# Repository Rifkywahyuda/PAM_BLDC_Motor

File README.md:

# PAM_BLDC_Motor
About design of PCB of Pulse Amplitude Modulation 
1. File "inverter#3" is a PCB controller that drive inverter 3 phase and buck converter to run motor BLDC
2. File "Buck#3" is a PCB mosfet area

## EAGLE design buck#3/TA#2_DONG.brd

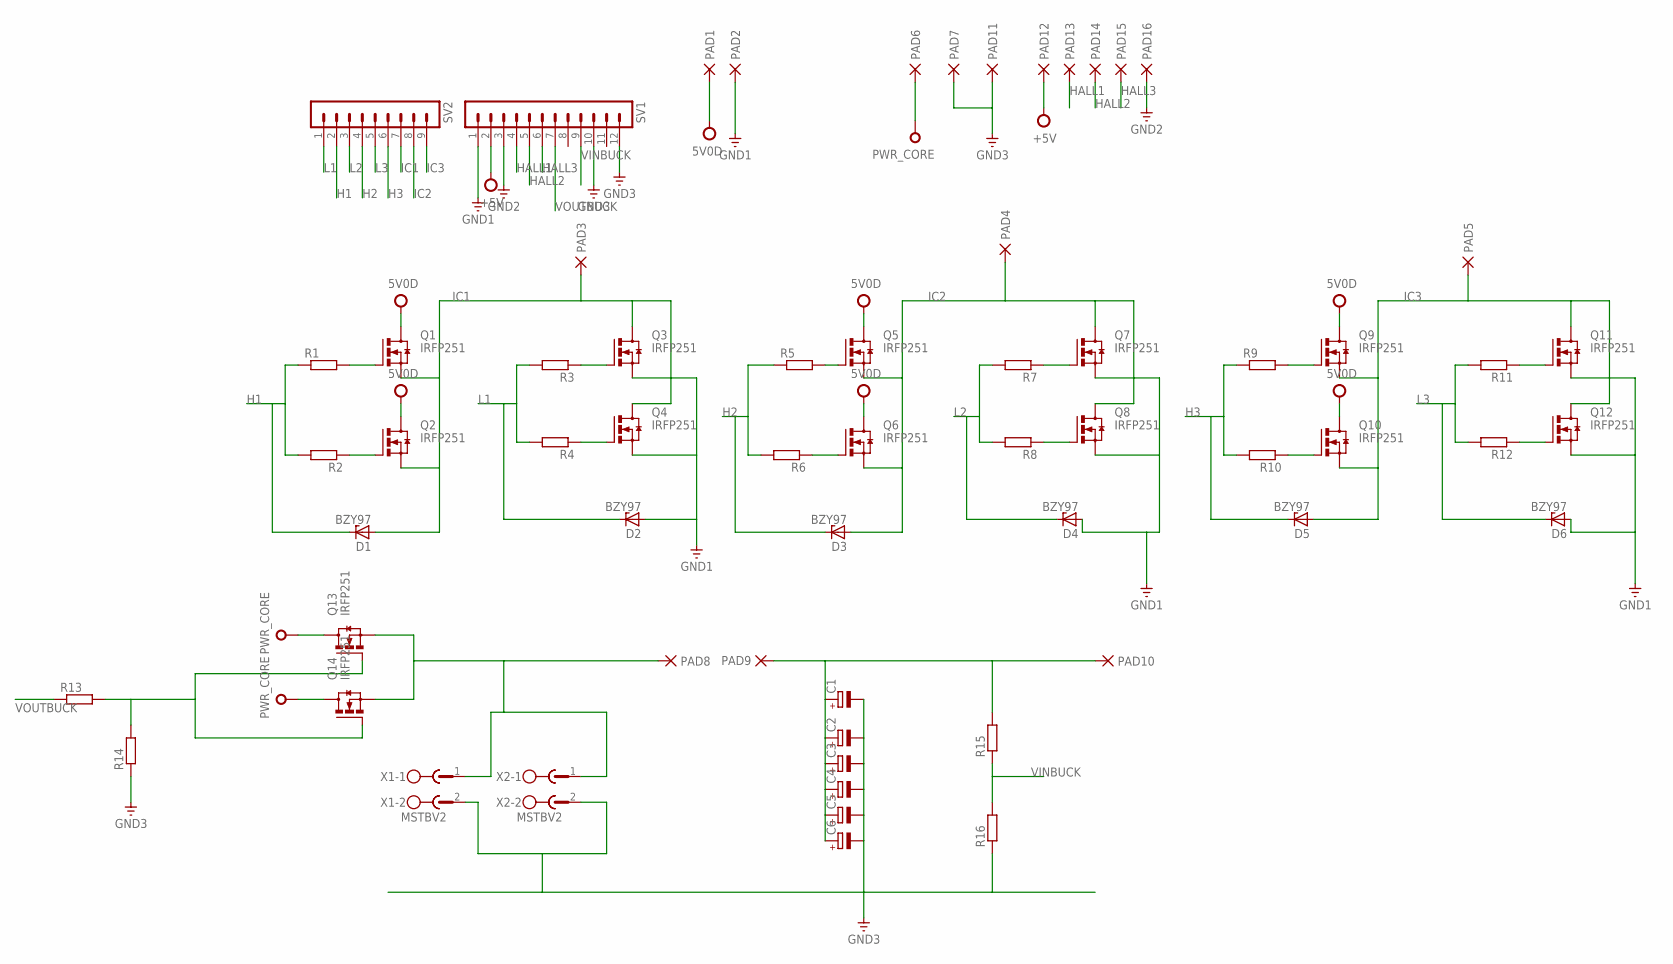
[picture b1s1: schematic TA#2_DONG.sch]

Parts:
C1, C2, C3, C4, C5, C6: CPOL-EUTT5D9; TT5D9
D1, D2, D3, D4, D5, D6: BZY97; F126Z12
PAD1, PAD2, PAD3, PAD4, PAD5, PAD6, PAD7, PAD8, PAD9, PAD10, PAD11, PAD12, PAD13, PAD14, PAD15, PAD16: PAD-0820; 0820
Q1, Q2, Q3, Q4, Q5, Q6, Q7, Q8, Q9, Q10, Q11, Q12, Q13, Q14: IRFP251; TO-247AD-V
R1, R2, R3, R4, R5, R6, R7, R8, R9, R10, R11, R12, R13, R14, R15, R16: R-EU_0207/15; 0207/15
SV1: MA12-1
SV2: MA09-1
X1, X2: MSTBV2

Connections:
5V0D: PAD1.P$1, Q1.D, Q2.D, Q5.D, Q6.D, Q9.D, Q10.D
+5V: PAD12.P$1, SV1.2
GND1: D2.A, D4.A, D6.A, PAD2.P$1, Q3.S, Q4.S, Q7.S, Q8.S, Q11.S, Q12.S, SV1.1
GND2: PAD16.P$1, SV1.3
GND3: C1.-, C2.-, C3.-, C4.-, C5.-, C6.-, PAD7.P$1, PAD11.P$1, R14.1, R16.1, SV1.10, SV1.12, X1.2, X2.2
H1: D1.C, R1.1, R2.2, SV2.2
H2: D3.C, R5.1, R6.2, SV2.4
H3: D5.C, R9.1, R10.2, SV2.6
HALL1: PAD13.P$1, SV1.4
HALL2: PAD14.P$1, SV1.5
HALL3: PAD15.P$1, SV1.6
IC1: D1.A, PAD3.P$1, Q1.S, Q2.S, Q3.D, Q4.D, SV2.7
IC2: D3.A, PAD4.P$1, Q5.S, Q6.S, Q7.D, Q8.D, SV2.8
IC3: D5.A, PAD5.P$1, Q9.S, Q10.S, Q11.D, Q12.D, SV2.9
L1: D2.C, R3.2, R4.2, SV2.1
L2: D4.C, R7.2, R8.2, SV2.3
L3: D6.C, R11.2, R12.2, SV2.5
unnamed: Q1.G, R1.2
unnamed: Q2.G, R2.1
unnamed: Q3.G, R3.1
unnamed: Q4.G, R4.1
unnamed: PAD8.P$1, Q13.S, Q14.S, X1.1, X2.1
unnamed: Q13.G, Q14.G, R13.2, R14.2
unnamed: Q5.G, R5.2
unnamed: C1.+, C2.+, C3.+, C4.+, C5.+, C6.+, PAD9.P$1, PAD10.P$1, R15.2
unnamed: Q6.G, R6.1
unnamed: Q7.G, R7.1
unnamed: Q8.G, R8.1
unnamed: Q9.G, R9.2
unnamed: Q10.G, R10.1
unnamed: Q11.G, R11.1
unnamed: Q12.G, R12.1
PWR_CORE: PAD6.P$1, Q13.D, Q14.D
VINBUCK: R15.1, R16.2, SV1.9
VOUTBUCK: R13.1, SV1.7

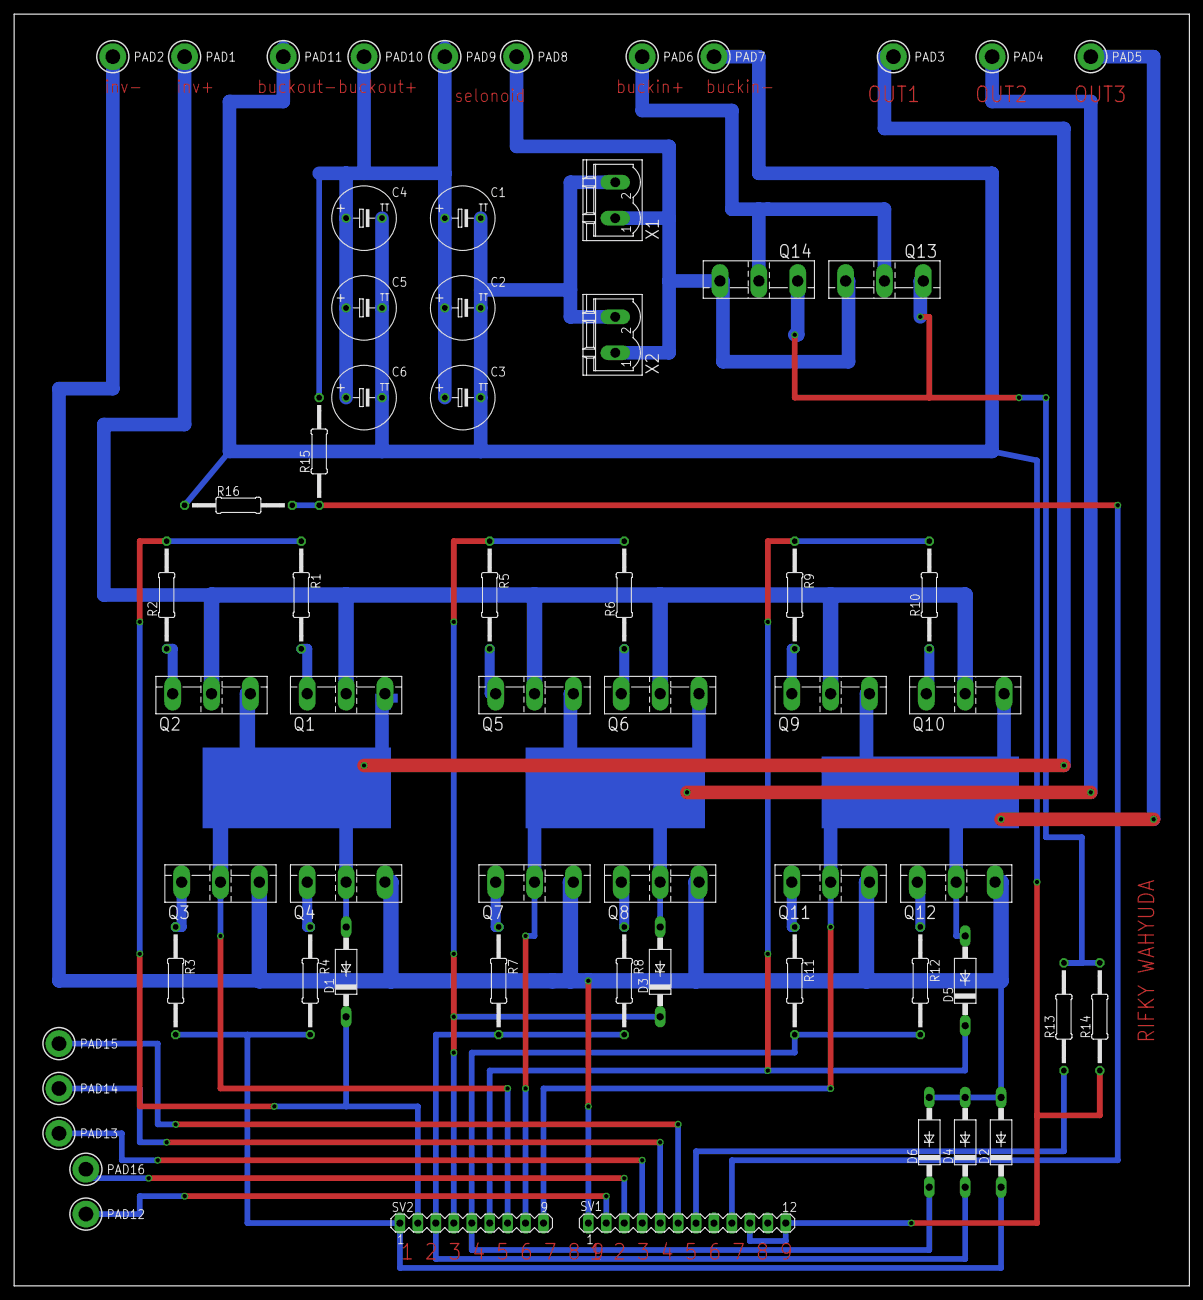
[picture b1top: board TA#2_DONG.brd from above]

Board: 2 copper layers, 166.3 x 180.0 mm, 62 parts (0 on the bottom side), 35 nets.

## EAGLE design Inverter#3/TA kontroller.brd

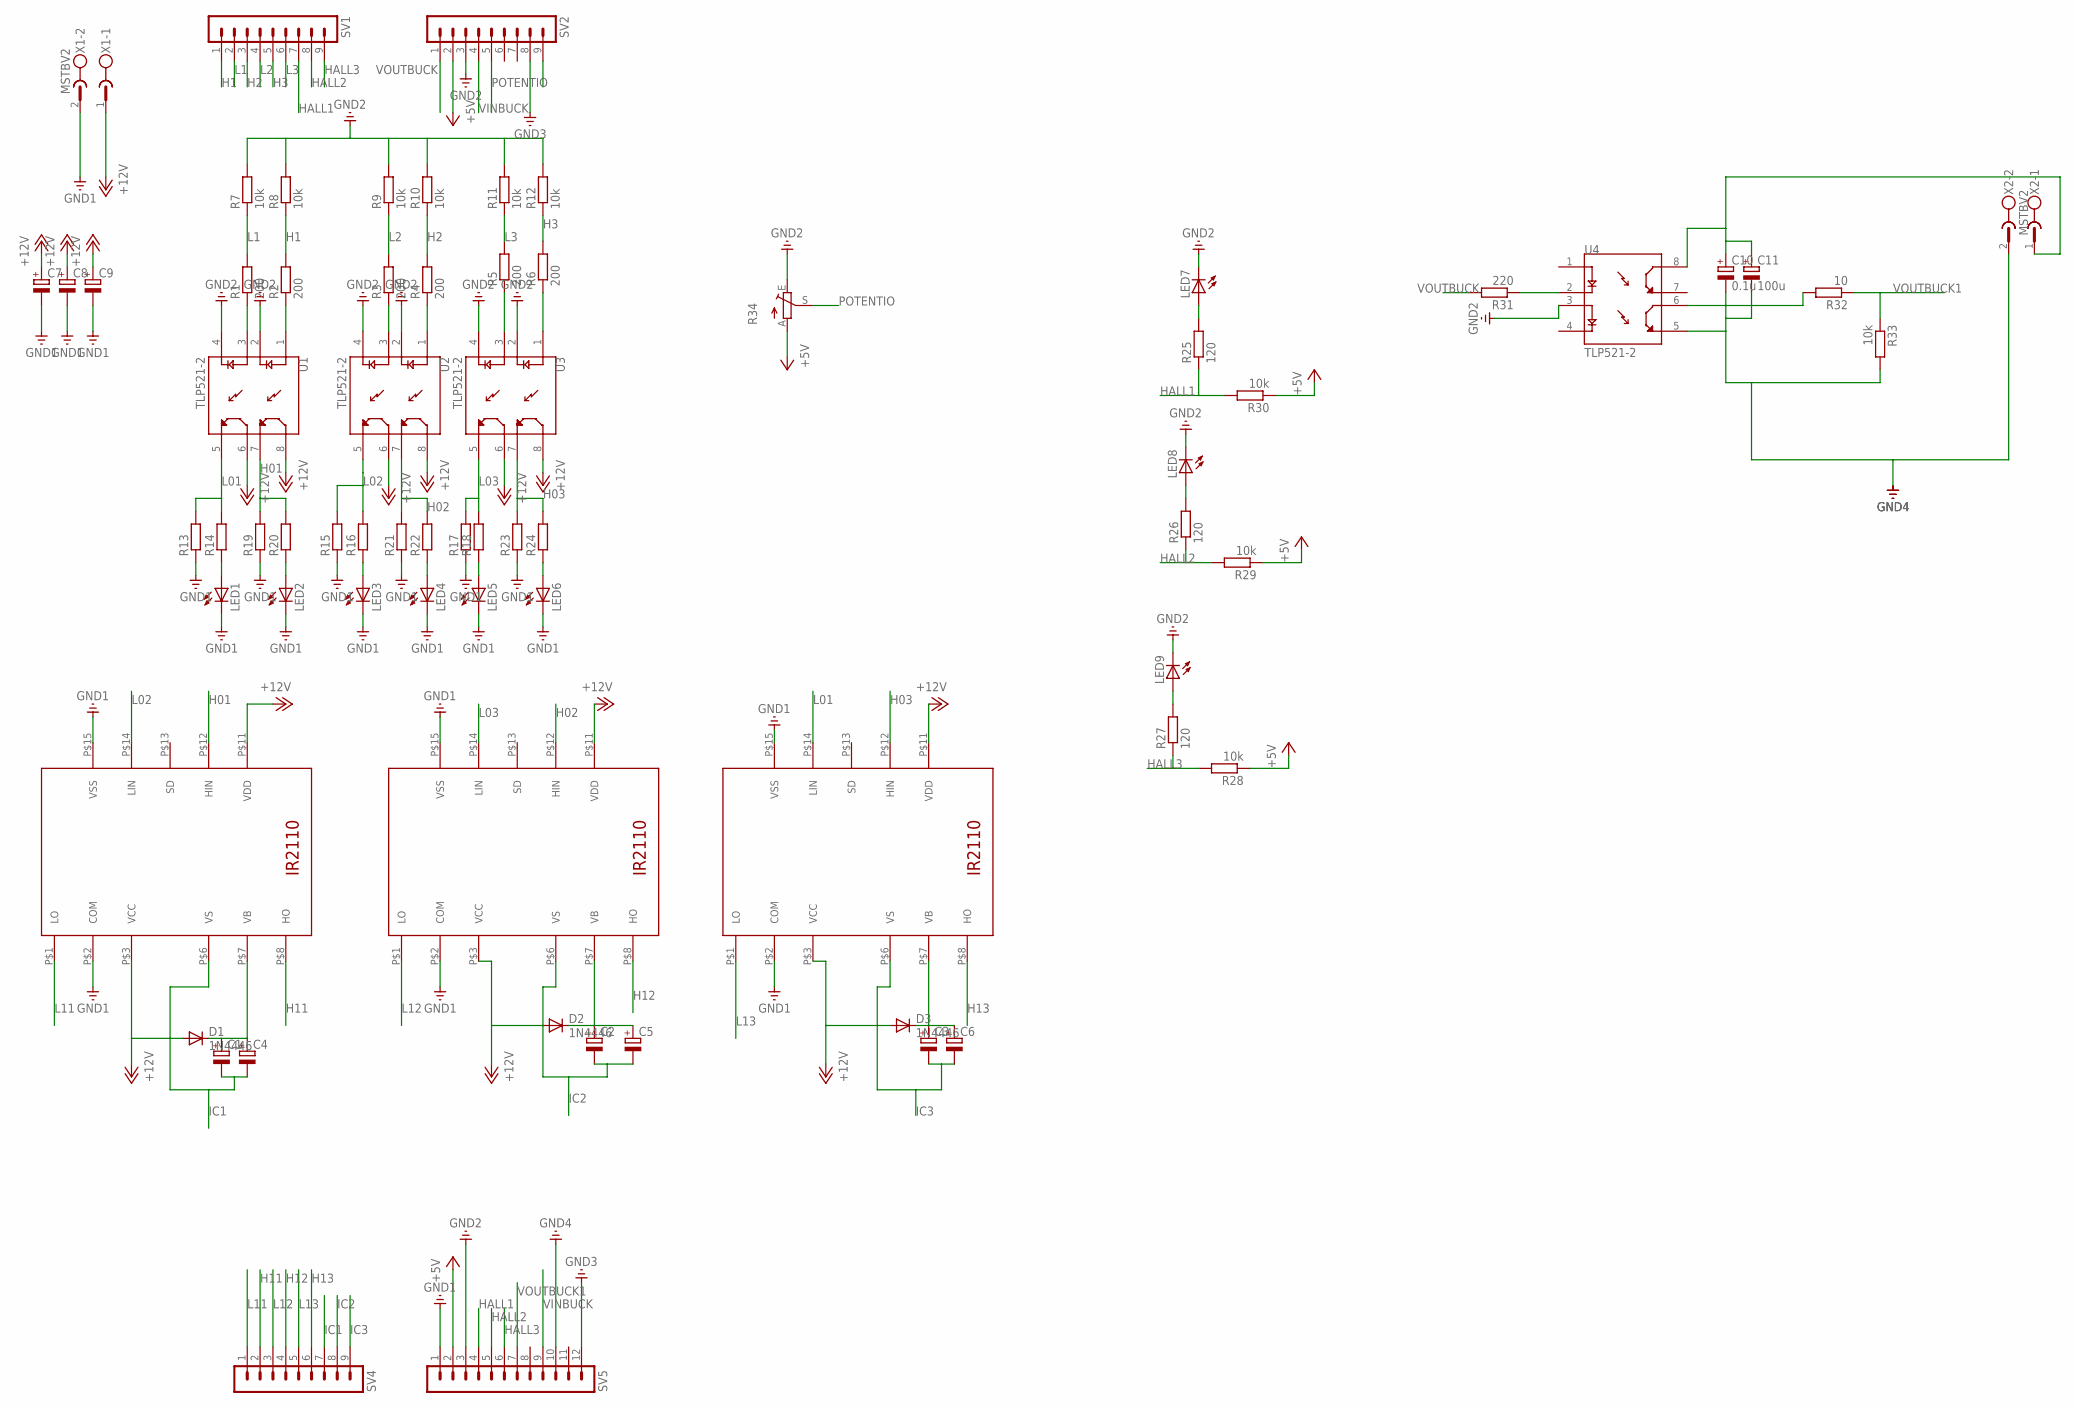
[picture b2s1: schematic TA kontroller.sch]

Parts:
C1, C2, C3, C4, C5, C6, C7, C8, C9: CPOL-EUB45181C; B45181C
C10: 0.1u; B45181C
C11: 100u; B45181C
D1, D2, D3: 1N4446; DO35-10
LED1, LED2, LED3, LED4, LED5, LED6, LED7, LED8, LED9: LED3MM
R1, R2, R3, R4, R5, R6: 200; 0207/12
R7, R8, R9, R10, R11, R12, R28, R29, R30, R33: 10k; 0207/12
R13, R14, R15, R16, R17, R18, R19, R20, R21, R22, R23, R24: R-EU_0207/12; 0207/12
R25, R26, R27: 120; 0207/12
R31: 220; 0207/12
R32: 10; 0207/12
R34: TRIM_EU-B25V; B25V
SV1, SV2, SV4: MA09-1
SV5: MA12-1
U1, U2, U3, U4: TLP521-2; DIP762W50P254L1018H451Q8
U$1, U$2, U$3: IR2110; DIL16
X1, X2: MSTBV2

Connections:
+5V: R28.1, R29.1, R30.1, R34.A, SV2.2, SV5.2
+12V: C7.+, C8.+, C9.+, D1.A, D2.A, D3.A, U1.6, U1.8, U2.6, U2.8, U3.6, U3.8, U$1.P$3 (VCC), U$1.P$11 (VDD), U$2.P$3 (VCC), U$2.P$11 (VDD), U$3.P$3 (VCC), U$3.P$11 (VDD), X1.1
GND1: C7.-, C8.-, C9.-, LED1.K (C), LED2.K (C), LED3.K (C), LED4.K (C), LED5.K (C), LED6.K (C), R13.1, R15.1, R17.1, R19.1, R21.1, R23.1, SV5.1, U$1.P$2 (COM), U$1.P$15 (VSS), U$2.P$2 (COM), U$2.P$15 (VSS), U$3.P$2 (COM), U$3.P$15 (VSS), X1.2
GND2: LED7.K (C), LED8.K (C), LED9.K (C), R7.2, R8.2, R9.2, R10.2, R11.2, R12.2, R34.E, SV2.3, SV5.3, U1.2, U1.4, U2.2, U2.4, U3.2, U3.4, U4.3
GND3: SV2.8, SV5.12
GND4: C10.-, C11.-, R33.2, SV5.10, U4.5, X2.2
H1: R2.2, R8.1, SV1.1
H01: R19.2, R20.2, U1.7, U$1.P$12 (HIN)
H2: R4.2, R10.1, SV1.3
H02: R21.2, R22.2, U2.7, U$2.P$12 (HIN)
H3: R6.2, R12.1, SV1.5
H03: R23.2, R24.2, U3.7, U$3.P$12 (HIN)
H11: SV4.2, U$1.P$8 (HO)
H12: SV4.4, U$2.P$8 (HO)
H13: SV4.6, U$3.P$8 (HO)
HALL1: R25.1, R30.2, SV1.7, SV5.4
HALL2: R26.1, R29.2, SV1.8, SV5.5
HALL3: R27.1, R28.2, SV1.9, SV5.6
IC1: C1.-, C4.-, SV4.7, U$1.P$6 (VS)
IC2: C2.-, C5.-, SV4.8, U$2.P$6 (VS)
IC3: C3.-, C6.-, SV4.9, U$3.P$6 (VS)
L1: R1.2, R7.1, SV1.2
L01: R13.2, R14.2, U1.5, U$3.P$14 (LIN)
L2: R3.2, R9.1, SV1.4
L02: R15.2, R16.2, U2.5, U$1.P$14 (LIN)
L3: R5.2, R11.1, SV1.6
L03: R17.2, R18.2, U3.5, U$2.P$14 (LIN)
L11: SV4.1, U$1.P$1 (LO)
L12: SV4.3, U$2.P$1 (LO)
L13: SV4.5, U$3.P$1 (LO)
unnamed: R2.1, U1.1
unnamed: R4.1, U2.1
unnamed: R32.2, U4.6
unnamed: R5.1, U3.3
unnamed: R6.1, U3.1
unnamed: LED1.A, R14.1
unnamed: LED2.A, R20.1
unnamed: LED3.A, R16.1
unnamed: LED4.A, R22.1
unnamed: R3.1, U2.3
unnamed: R1.1, U1.3
unnamed: LED5.A, R18.1
unnamed: LED6.A, R24.1
unnamed: R31.1, U4.2
unnamed: C2.+, C5.+, D2.C, U$2.P$7 (VB)
unnamed: C1.+, C4.+, D1.C, U$1.P$7 (VB)
unnamed: C3.+, C6.+, D3.C, U$3.P$7 (VB)
unnamed: LED9.A, R27.2
unnamed: LED8.A, R26.2
unnamed: LED7.A, R25.2
POTENTIO: R34.S, SV2.5
V2: C10.+, C11.+, SV2.9, U4.8, X2.1
VINBUCK: SV2.4, SV5.9
VOUTBUCK: R31.2, SV2.1
VOUTBUCK1: R32.1, R33.1, SV5.7

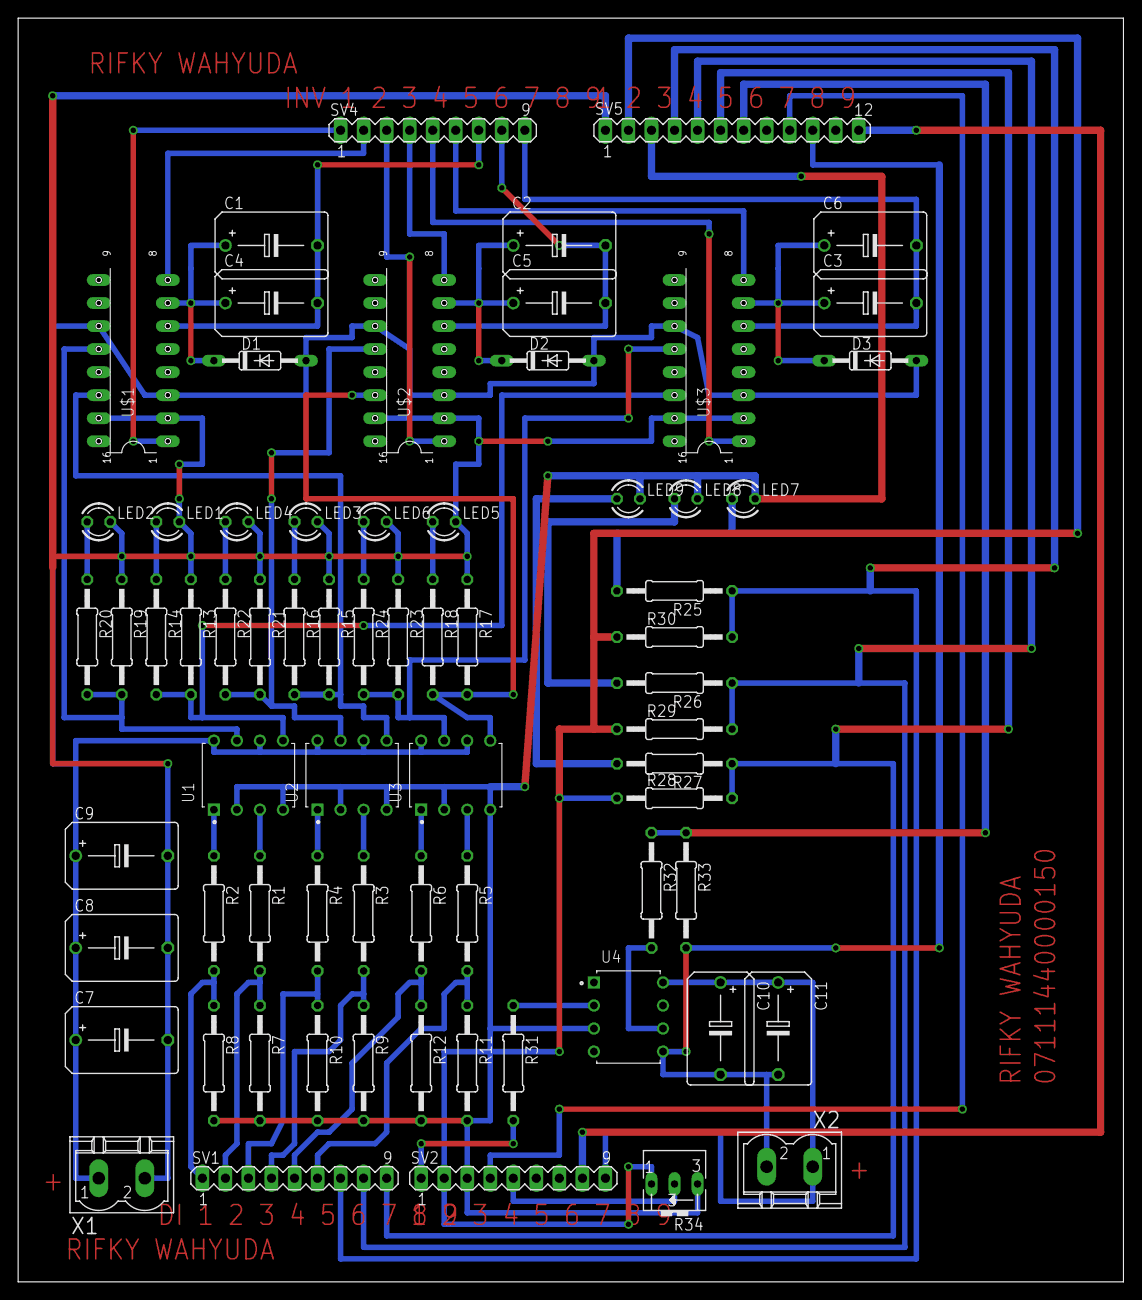
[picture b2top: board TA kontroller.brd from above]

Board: 2 copper layers, 121.9 x 139.4 mm, 70 parts (0 on the bottom side), 55 nets.

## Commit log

2020-05-24 Part of Controller
    This part is a controller area, that contains IC and part that can drive inverter 3 phase and buck converters.
2020-05-24 Mosfet Part
    This PCB contains many of mosfets that driven by controller to run the BLDC motor.

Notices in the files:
parts and their libraries:
supply0: Copyright (C) 2007, Bob Starr
dpads: Copyright (C) 2004, Bob Starr (bobstarr@mindspring.com)
